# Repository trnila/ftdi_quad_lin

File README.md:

# FTDI Quad LIN

FTDI Quad-LIN is an FTDI-based board that enables communication with up to 4 LIN channels.

- 4x LIN master channels
- USB-C connector
- channel LED indication of power presence and communication activity
- power jack to power selected transceiver and its network

## Getting started
Install dkms driver for sllin module:
```
$ ./install_driver.sh
```

Then run following commands to:
- write given serial number into the device
- install a udev rule to start `ldattach@.service` on USB plug-in
- copy `sllin.network` file to automatically bringup `slcan` interface up

```
$ sudo apt install ftdi-eeprom
$ ./setup.sh some_serial_number
```

## Tests

Connect all channels to 2x PCAN-USB Pro, then install peak driver:
```sh
$ wget https://www.peak-system.com/quick/PLIN-Linux-Driver -O plin_linux_driver.tar.gz
$ tar -xf plin_linux_driver.tar.gz
$ cd peak-lin-driver-1.4.0
$ make
$ sudo make install
```

Then test all channels as masters by sending frames to the connected PCAN-USB device:
```
$ uv run pytest
```

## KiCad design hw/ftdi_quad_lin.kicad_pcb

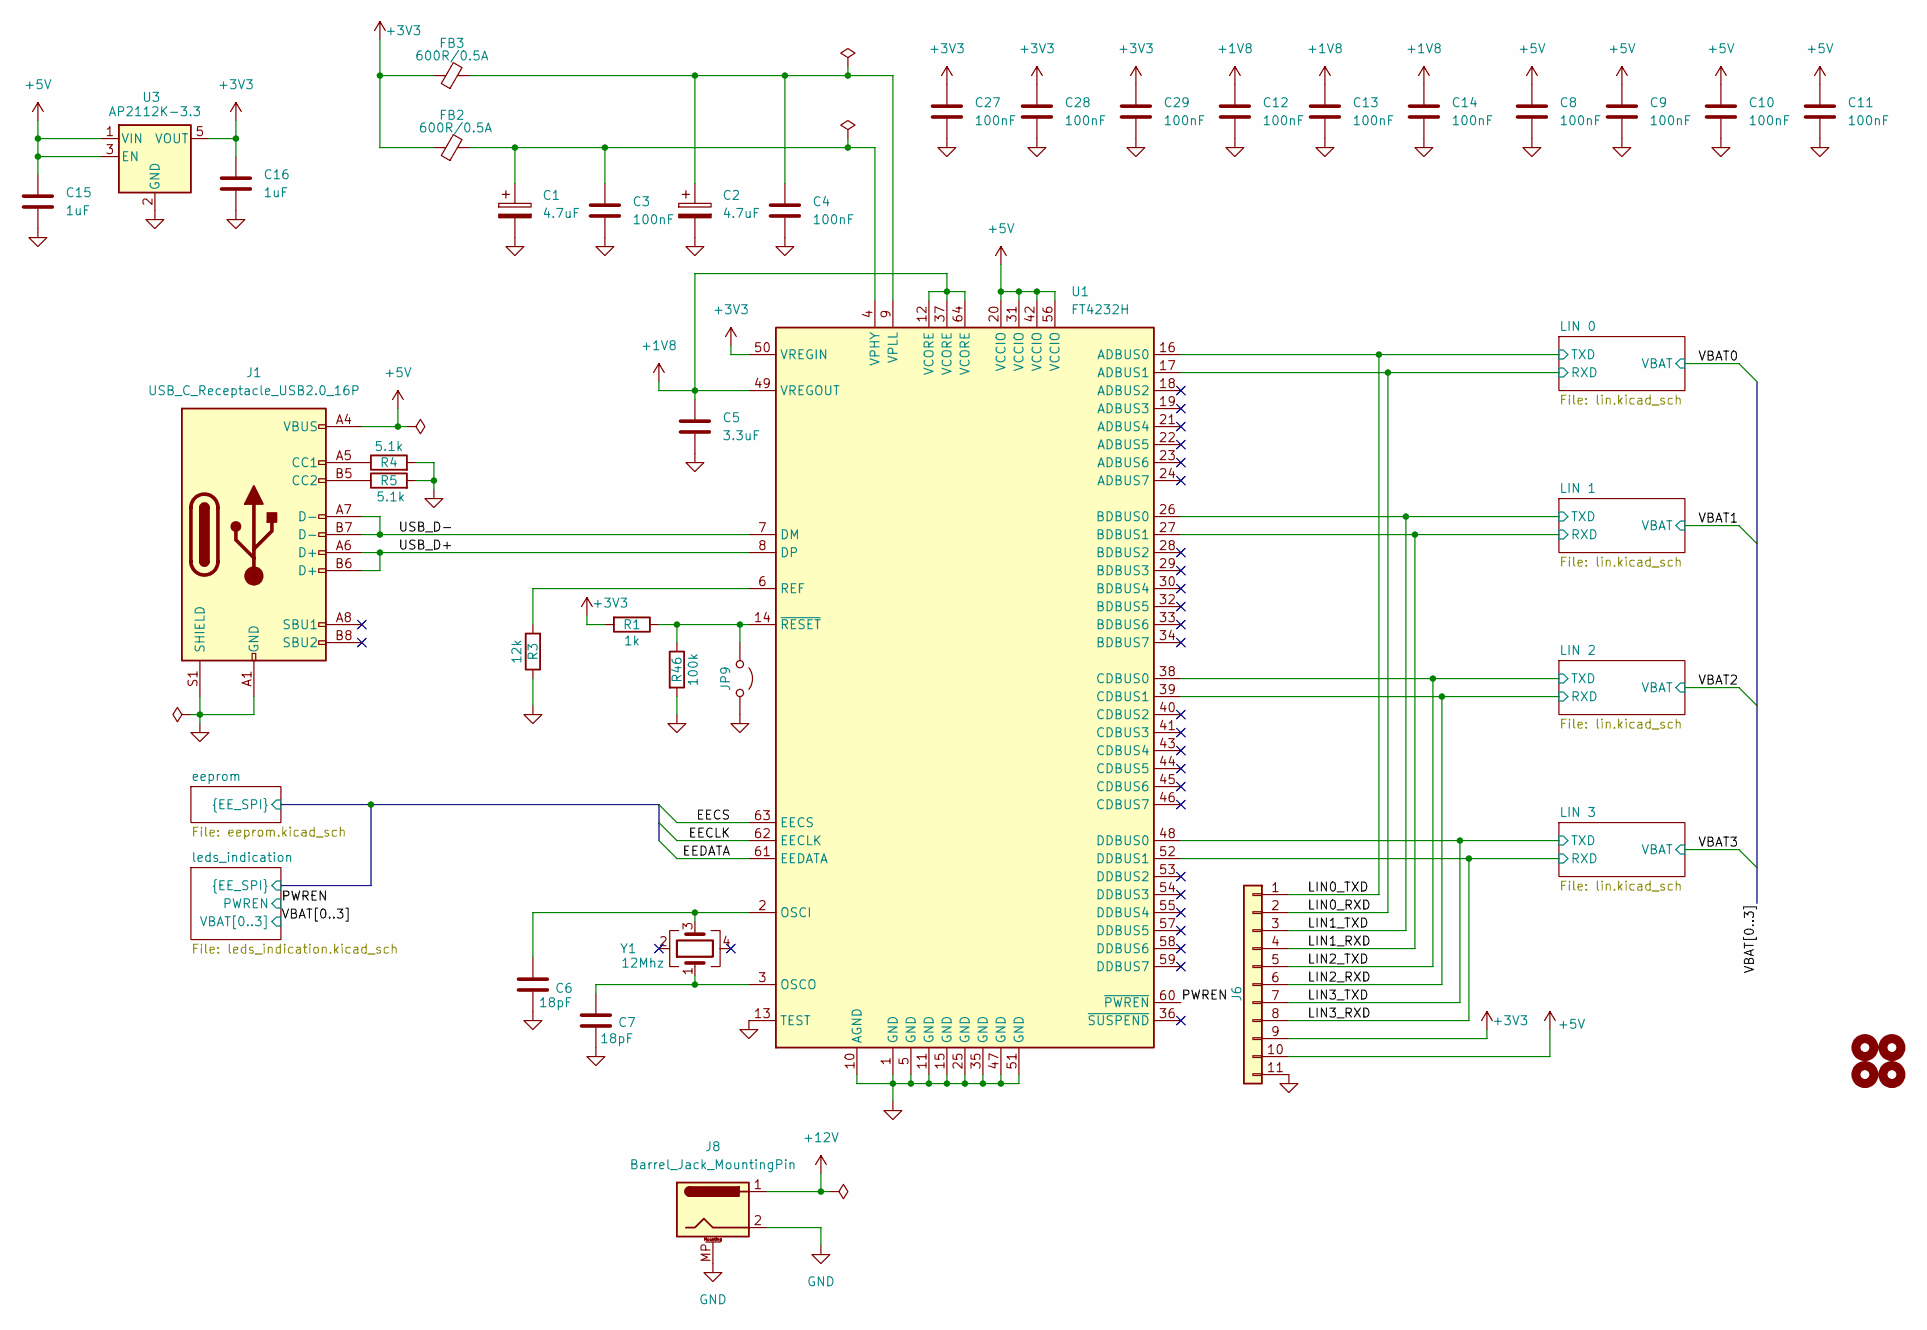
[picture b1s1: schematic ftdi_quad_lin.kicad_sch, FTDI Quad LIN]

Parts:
C1, C2: 4.7uF; C_1206_3216Metric_Pad1.33x1.80mm_HandSolder
C3, C4, C8, C9, C10, C11, C12, C13, C14, C27, C28, C29: 100nF; C_0805_2012Metric
C5: 3.3uF; C_0805_2012Metric
C6, C7: 18pF; C_0805_2012Metric
C15, C16: 1uF; C_0805_2012Metric
FB2, FB3: 600R/0.5A; L_0603_1608Metric_Pad1.05x0.95mm_HandSolder
H1, H2, H3, H4: MountingHole; MountingHole_3.2mm_M3
J1: USB_C_Receptacle_USB2.0_16P; USB_C_Receptacle_GCT_USB4105-xx-A_16P_TopMnt_Horizontal
J6: Conn_01x10; PinHeader_1x11_P2.54mm_Vertical
J8: Barrel_Jack_MountingPin; BarrelJack_CUI_PJ-063AH_Horizontal
JP9: Jumper_2_Open; TestPoint_2Pads_Pitch2.54mm_Drill0.8mm
R1: 1k; R_0805_2012Metric
R3: 12k; R_0805_2012Metric
R4, R5: 5.1k; R_0805_2012Metric
R46: 100k; R_0805_2012Metric
U1: FT4232H; LQFP-64_10x10mm_P0.5mm
U3: AP2112K-3.3; SOT-23-5_HandSoldering
Y1: 12Mhz; Crystal_SMD_TXC_7M-4Pin_3.2x2.5mm_HandSoldering

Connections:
+1V8: C5.1, C12.1, C13.1, C14.1, U1.12 (VCORE), U1.37 (VCORE), U1.49 (VREGOUT), U1.64 (VCORE)
+3V3: C16.1, C27.1, C28.1, C29.1, FB2.1, FB3.1, J6.9, R1.2, U1.50 (VREGIN), U3.5 (VOUT)
+5V: C8.1, C9.1, C10.1, C11.1, C15.1, J1.A4 (VBUS), J1.A9 (VBUS), J1.B4 (VBUS), J1.B9 (VBUS), J6.10, U1.20 (VCCIO), U1.31 (VCCIO), U1.42 (VCCIO), U1.56 (VCCIO), U3.1 (VIN), U3.3 (EN); also elsewhere on the board
+12V: J8.1; also elsewhere on the board
/LIN0_RXD: J6.2, U1.17 (ADBUS1); also elsewhere on the board
/LIN0_TXD: J6.1, U1.16 (ADBUS0); also elsewhere on the board
/LIN1_RXD: J6.4, U1.27 (BDBUS1); also elsewhere on the board
/LIN1_TXD: J6.3, U1.26 (BDBUS0); also elsewhere on the board
/LIN2_RXD: J6.6, U1.39 (CDBUS1); also elsewhere on the board
/LIN2_TXD: J6.5, U1.38 (CDBUS0); also elsewhere on the board
/LIN3_RXD: J6.8, U1.52 (DDBUS1); also elsewhere on the board
/LIN3_TXD: J6.7, U1.48 (DDBUS0); also elsewhere on the board
/PWREN: U1.60 (~PWREN); also elsewhere on the board
/USB_D+: J1.A6 (D+), J1.B6 (D+), U1.8 (DP)
/USB_D-: J1.A7 (D-), J1.B7 (D-), U1.7 (DM)
/eeprom/EECLK: U1.62 (EECLK); also elsewhere on the board
/eeprom/EECS: U1.63 (EECS); also elsewhere on the board
/eeprom/EEDATA: U1.61 (EEDATA); also elsewhere on the board
GND: C1.2, C2.2, C3.2, C4.2, C5.2, C6.2, C7.2, C8.2, C9.2, C10.2, C11.2, C12.2, C13.2, C14.2, C15.2, C16.2, C27.2, C28.2, C29.2, J1.A1 (GND), J1.A12 (GND), J1.B1 (GND), J1.B12 (GND), J1.S1 (SHIELD), J6.11, J8.2, J8.MP (MountPin), JP9.2 (B), R3.1, R4.2, R5.2, R46.2, U1.1 (GND), U1.5 (GND), U1.10 (AGND), U1.11 (GND), U1.13 (TEST), U1.15 (GND), U1.25 (GND), U1.35 (GND), U1.47 (GND), U1.51 (GND), U3.2 (GND); also elsewhere on the board
unnamed: J1.A5 (CC1), R4.1
unnamed: J1.B5 (CC2), R5.1
unnamed: JP9.1 (A), R1.1, R46.1, U1.14 (~RESET)
unnamed: C6.1, U1.2 (OSCI), Y1.3
unnamed: C7.1, U1.3 (OSCO), Y1.1
unnamed: R3.2, U1.6 (REF)
unnamed: C1.1, C3.1, FB2.2, U1.4 (VPHY)
unnamed: C2.1, C4.1, FB3.2, U1.9 (VPLL)

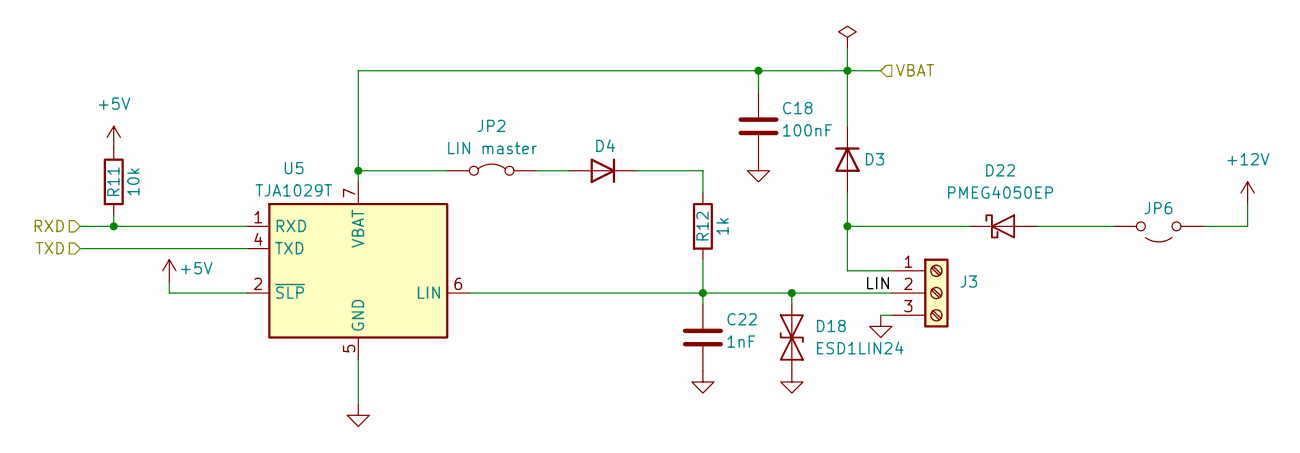
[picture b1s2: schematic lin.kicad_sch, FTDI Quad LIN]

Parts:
C18: 100nF; C_0805_2012Metric
C22: 1nF; C_0805_2012Metric
D3, D4: D_SOD-323_HandSoldering
D18: ESD1LIN24; D_SOD-323_HandSoldering
D22: PMEG4050EP; Nexperia_CFP3_SOD-123W
J3: Screw_Terminal_01x03; lin_connector
JP2: LIN master; TestPoint_2Pads_Pitch2.54mm_Drill0.8mm
JP6: Jumper_2_Open; TestPoint_2Pads_Pitch2.54mm_Drill0.8mm
R11: 10k; R_0805_2012Metric
R12: 1k; R_0805_2012Metric
U5: TJA1029T; SOIC-8_3.9x4.9mm_P1.27mm

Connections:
+5V: R11.1, U5.2 (~SLP); also elsewhere on the board
+12V: JP6.1 (A); also elsewhere on the board
/LIN1_RXD: R11.2, U5.1 (RXD); also elsewhere on the board
/LIN1_TXD: U5.4 (TXD); also elsewhere on the board
/LIN 1/LIN: C22.1, D18.2 (A2), J3.2, R12.2, U5.6 (LIN)
/VBAT1: C18.1, D3.1 (K), JP2.1 (A), U5.7 (VBAT); also elsewhere on the board
GND: C18.2, C22.2, D18.1 (A1), J3.3, U5.5 (GND); also elsewhere on the board
unnamed: D4.2 (A), JP2.2 (B)
unnamed: D4.1 (K), R12.1
unnamed: D22.2 (A), JP6.2 (B)
unnamed: D3.2 (A), D22.1 (K), J3.1

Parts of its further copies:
C17, C19, C20: 100nF; C_0805_2012Metric
C21, C23, C24: 1nF; C_0805_2012Metric
D1, D2, D5, D6, D7, D8: D_SOD-323_HandSoldering
D9, D19, D20: ESD1LIN24; D_SOD-323_HandSoldering
D21, D23, D24: PMEG4050EP; Nexperia_CFP3_SOD-123W
J2, J4, J5: Screw_Terminal_01x03; lin_connector
JP1, JP3, JP4: LIN master; TestPoint_2Pads_Pitch2.54mm_Drill0.8mm
JP5, JP7, JP8: Jumper_2_Open; TestPoint_2Pads_Pitch2.54mm_Drill0.8mm
R9, R13, R15: 10k; R_0805_2012Metric
R10, R14, R16: 1k; R_0805_2012Metric
U2, U6, U7: TJA1029T; SOIC-8_3.9x4.9mm_P1.27mm

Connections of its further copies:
+5V: R9.1, R13.1, R15.1, U2.2 (~SLP), U6.2 (~SLP), U7.2 (~SLP); also elsewhere on the board
+12V: JP5.1 (A), JP7.1 (A), JP8.1 (A); also elsewhere on the board
/LIN0_RXD: R9.2, U2.1 (RXD); also elsewhere on the board
/LIN0_TXD: U2.4 (TXD); also elsewhere on the board
/LIN2_RXD: R13.2, U6.1 (RXD); also elsewhere on the board
/LIN2_TXD: U6.4 (TXD); also elsewhere on the board
/LIN3_RXD: R15.2, U7.1 (RXD); also elsewhere on the board
/LIN3_TXD: U7.4 (TXD); also elsewhere on the board
/LIN 0/LIN: C21.1, D9.2 (A2), J2.2, R10.2, U2.6 (LIN)
/LIN 2/LIN: C23.1, D19.2 (A2), J4.2, R14.2, U6.6 (LIN)
/LIN 3/LIN: C24.1, D20.2 (A2), J5.2, R16.2, U7.6 (LIN)
/VBAT0: C17.1, D1.1 (K), JP1.1 (A), U2.7 (VBAT); also elsewhere on the board
/VBAT2: C19.1, D5.1 (K), JP3.1 (A), U6.7 (VBAT); also elsewhere on the board
/VBAT3: C20.1, D7.1 (K), JP4.1 (A), U7.7 (VBAT); also elsewhere on the board
GND: C17.2, C19.2, C20.2, C21.2, C23.2, C24.2, D9.1 (A1), D19.1 (A1), D20.1 (A1), J2.3, J4.3, J5.3, U2.5 (GND), U6.5 (GND), U7.5 (GND); also elsewhere on the board
unnamed: D1.2 (A), D21.1 (K), J2.1
unnamed: D2.2 (A), JP1.2 (B)
unnamed: D2.1 (K), R10.1
unnamed: D6.2 (A), JP3.2 (B)
unnamed: D6.1 (K), R14.1
unnamed: D8.2 (A), JP4.2 (B)
unnamed: D8.1 (K), R16.1
unnamed: D21.2 (A), JP5.2 (B)
unnamed: D23.2 (A), JP7.2 (B)
unnamed: D5.2 (A), D23.1 (K), J4.1
unnamed: D24.2 (A), JP8.2 (B)
unnamed: D7.2 (A), D24.1 (K), J5.1

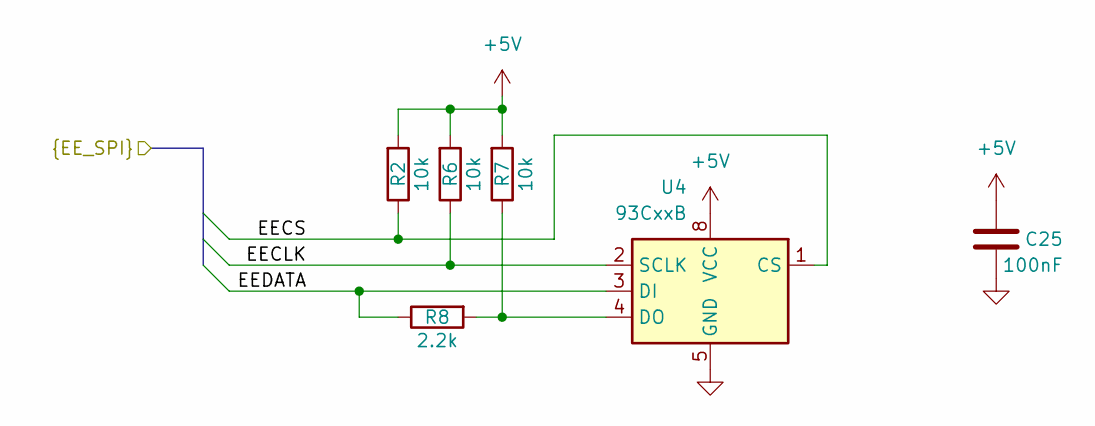
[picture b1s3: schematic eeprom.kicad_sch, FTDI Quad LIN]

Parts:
C25: 100nF; C_0805_2012Metric
R2, R6, R7: 10k; R_0805_2012Metric
R8: 2.2k; R_0805_2012Metric
U4: 93CxxB; SOIC-8_3.9x4.9mm_P1.27mm

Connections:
+5V: C25.1, R2.2, R6.2, R7.2, U4.8 (VCC); also elsewhere on the board
/eeprom/EECLK: R6.1, U4.2 (SCLK); also elsewhere on the board
/eeprom/EECS: R2.1, U4.1 (CS); also elsewhere on the board
/eeprom/EEDATA: R8.1, U4.3 (DI); also elsewhere on the board
GND: C25.2, U4.5 (GND); also elsewhere on the board
unnamed: R7.1, R8.2, U4.4 (DO)

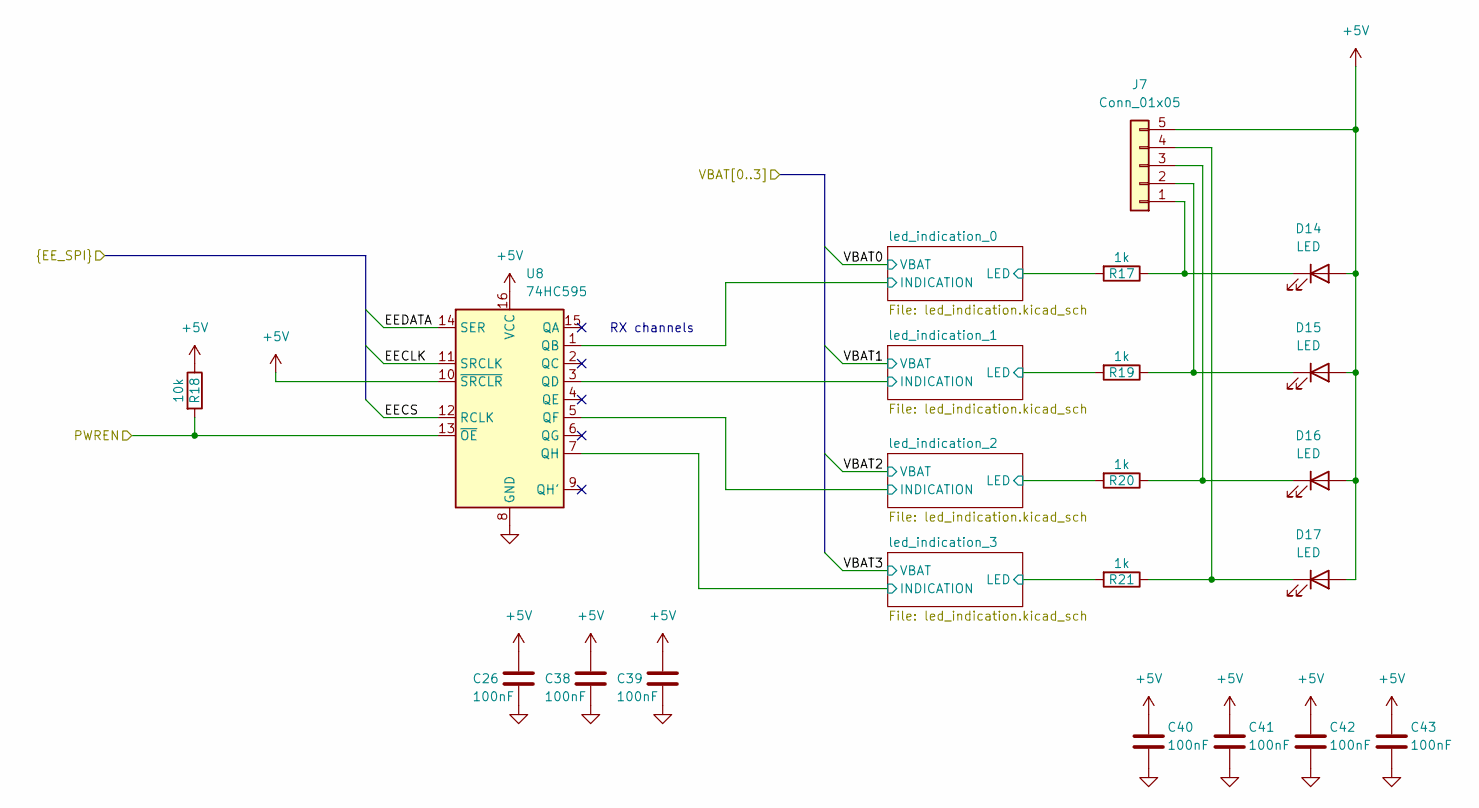
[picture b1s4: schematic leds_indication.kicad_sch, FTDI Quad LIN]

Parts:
C26, C38, C39, C40, C41, C42, C43: 100nF; C_0805_2012Metric
D14, D15, D16, D17: LED; 1216.1002
J7: Conn_01x05; JST_XH_B5B-XH-A_1x05_P2.50mm_Vertical
R17, R19, R20, R21: 1k; R_0805_2012Metric
R18: 10k; R_0805_2012Metric
U8: 74HC595; SOIC-16_3.9x9.9mm_P1.27mm

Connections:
+5V: C26.1, C38.1, C39.1, C40.1, C41.1, C42.1, C43.1, D14.2 (A), D15.2 (A), D16.2 (A), D17.2 (A), J7.5, R18.1, U8.10 (~SRCLR), U8.16 (VCC); also elsewhere on the board
/PWREN: R18.2, U8.13 (~OE); also elsewhere on the board
/eeprom/EECLK: U8.11 (SRCLK); also elsewhere on the board
/eeprom/EECS: U8.12 (RCLK); also elsewhere on the board
/eeprom/EEDATA: U8.14 (SER); also elsewhere on the board
/leds_indication/led_indication_0/INDICATION: U8.1 (QB); also elsewhere on the board
/leds_indication/led_indication_0/LED: R17.2; also elsewhere on the board
/leds_indication/led_indication_1/INDICATION: U8.3 (QD); also elsewhere on the board
/leds_indication/led_indication_1/LED: R19.2; also elsewhere on the board
/leds_indication/led_indication_2/INDICATION: U8.5 (QF); also elsewhere on the board
/leds_indication/led_indication_2/LED: R20.2; also elsewhere on the board
/leds_indication/led_indication_3/INDICATION: U8.7 (QH); also elsewhere on the board
/leds_indication/led_indication_3/LED: R21.2; also elsewhere on the board
GND: C26.2, C38.2, C39.2, C40.2, C41.2, C42.2, C43.2, U8.8 (GND); also elsewhere on the board
unnamed: D14.1 (K), J7.1, R17.1
unnamed: D15.1 (K), J7.2, R19.1
unnamed: D16.1 (K), J7.3, R20.1
unnamed: D17.1 (K), J7.4, R21.1

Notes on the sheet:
RX channels

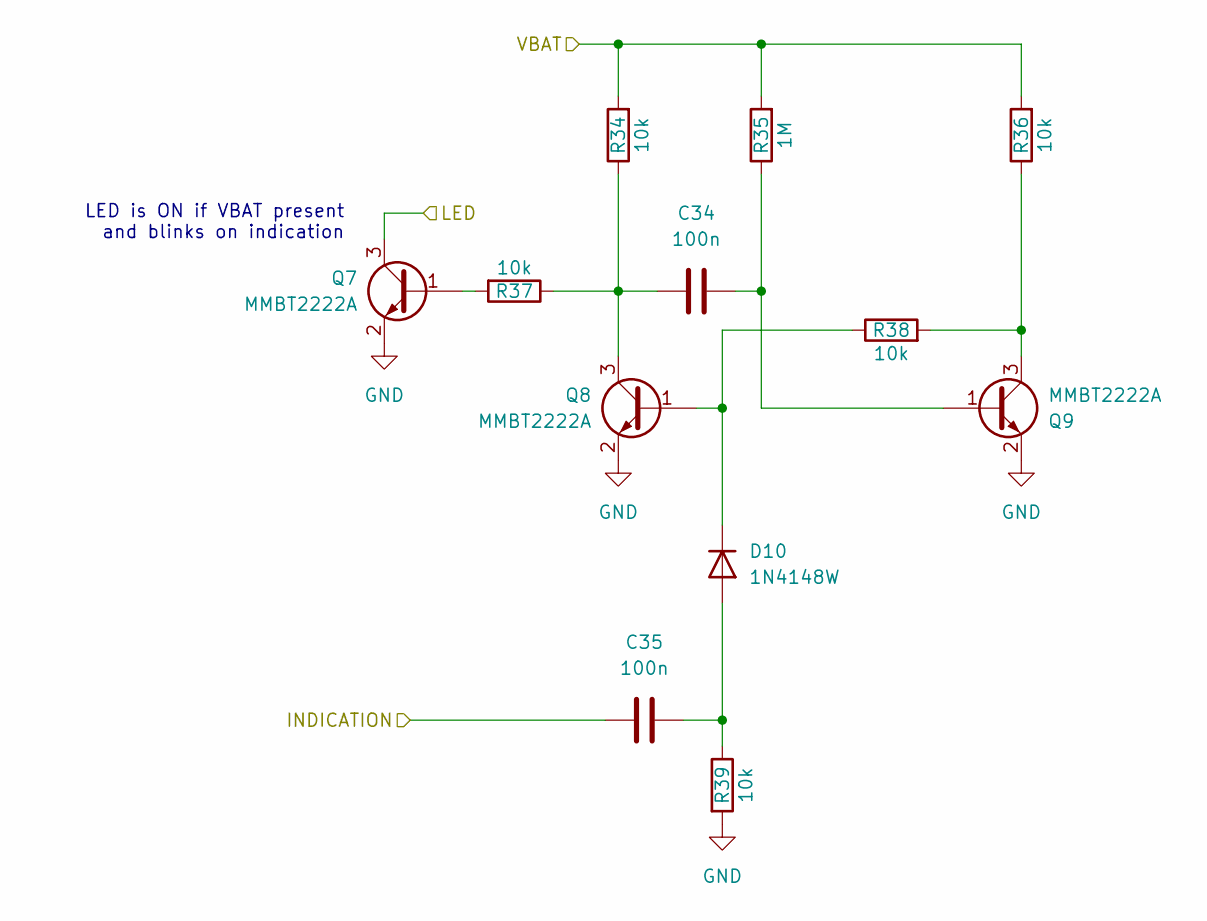
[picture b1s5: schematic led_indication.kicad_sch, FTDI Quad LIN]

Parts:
C34, C35: 100n; C_0805_2012Metric_Pad1.18x1.45mm_HandSolder
D10: 1N4148W; D_SOD-323_HandSoldering
Q7, Q8, Q9: MMBT2222A; SOT-23
R34, R36, R37, R38, R39: 10k; R_0805_2012Metric
R35: 1M; R_0805_2012Metric

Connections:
/VBAT2: R34.2, R35.2, R36.2; also elsewhere on the board
/leds_indication/led_indication_2/INDICATION: C35.1; also elsewhere on the board
/leds_indication/led_indication_2/LED: Q7.3 (C); also elsewhere on the board
GND: Q7.2 (E), Q8.2 (E), Q9.2 (E), R39.2; also elsewhere on the board
unnamed: C35.2, D10.2 (A), R39.1
unnamed: D10.1 (K), Q8.1 (B), R38.1
unnamed: Q7.1 (B), R37.2
unnamed: C34.1, Q8.3 (C), R34.1, R37.1
unnamed: C34.2, Q9.1 (B), R35.1
unnamed: Q9.3 (C), R36.1, R38.2

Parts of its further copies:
C30, C31, C32, C33, C36, C37: 100n; C_0805_2012Metric_Pad1.18x1.45mm_HandSolder
D11, D12, D13: 1N4148W; D_SOD-323_HandSoldering
Q1, Q2, Q3, Q4, Q5, Q6, Q10, Q11, Q12: MMBT2222A; SOT-23
R22, R24, R25, R26, R27, R28, R30, R31, R32, R33, R40, R42, R43, R44, R45: 10k; R_0805_2012Metric
R23, R29, R41: 1M; R_0805_2012Metric

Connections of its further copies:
/VBAT0: R22.2, R23.2, R24.2; also elsewhere on the board
/VBAT1: R28.2, R29.2, R30.2; also elsewhere on the board
/VBAT3: R40.2, R41.2, R42.2; also elsewhere on the board
/leds_indication/led_indication_0/INDICATION: C31.1; also elsewhere on the board
/leds_indication/led_indication_0/LED: Q1.3 (C); also elsewhere on the board
/leds_indication/led_indication_1/INDICATION: C33.1; also elsewhere on the board
/leds_indication/led_indication_1/LED: Q4.3 (C); also elsewhere on the board
/leds_indication/led_indication_3/INDICATION: C37.1; also elsewhere on the board
/leds_indication/led_indication_3/LED: Q10.3 (C); also elsewhere on the board
GND: Q1.2 (E), Q2.2 (E), Q3.2 (E), Q4.2 (E), Q5.2 (E), Q6.2 (E), Q10.2 (E), Q11.2 (E), Q12.2 (E), R27.2, R33.2, R45.2; also elsewhere on the board
unnamed: C31.2, D11.2 (A), R27.1
unnamed: D11.1 (K), Q2.1 (B), R26.1
unnamed: C33.2, D12.2 (A), R33.1
unnamed: D12.1 (K), Q5.1 (B), R32.1
unnamed: C37.2, D13.2 (A), R45.1
unnamed: D13.1 (K), Q11.1 (B), R44.1
unnamed: Q1.1 (B), R25.2
unnamed: C30.1, Q2.3 (C), R22.1, R25.1
unnamed: C30.2, Q3.1 (B), R23.1
unnamed: Q3.3 (C), R24.1, R26.2
unnamed: Q4.1 (B), R31.2
unnamed: C32.1, Q5.3 (C), R28.1, R31.1
unnamed: C32.2, Q6.1 (B), R29.1
unnamed: Q6.3 (C), R30.1, R32.2
unnamed: Q10.1 (B), R43.2
unnamed: C36.1, Q11.3 (C), R40.1, R43.1
unnamed: C36.2, Q12.1 (B), R41.1
unnamed: Q12.3 (C), R42.1, R44.2

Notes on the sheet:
LED is ON if VBAT present and blinks on indication

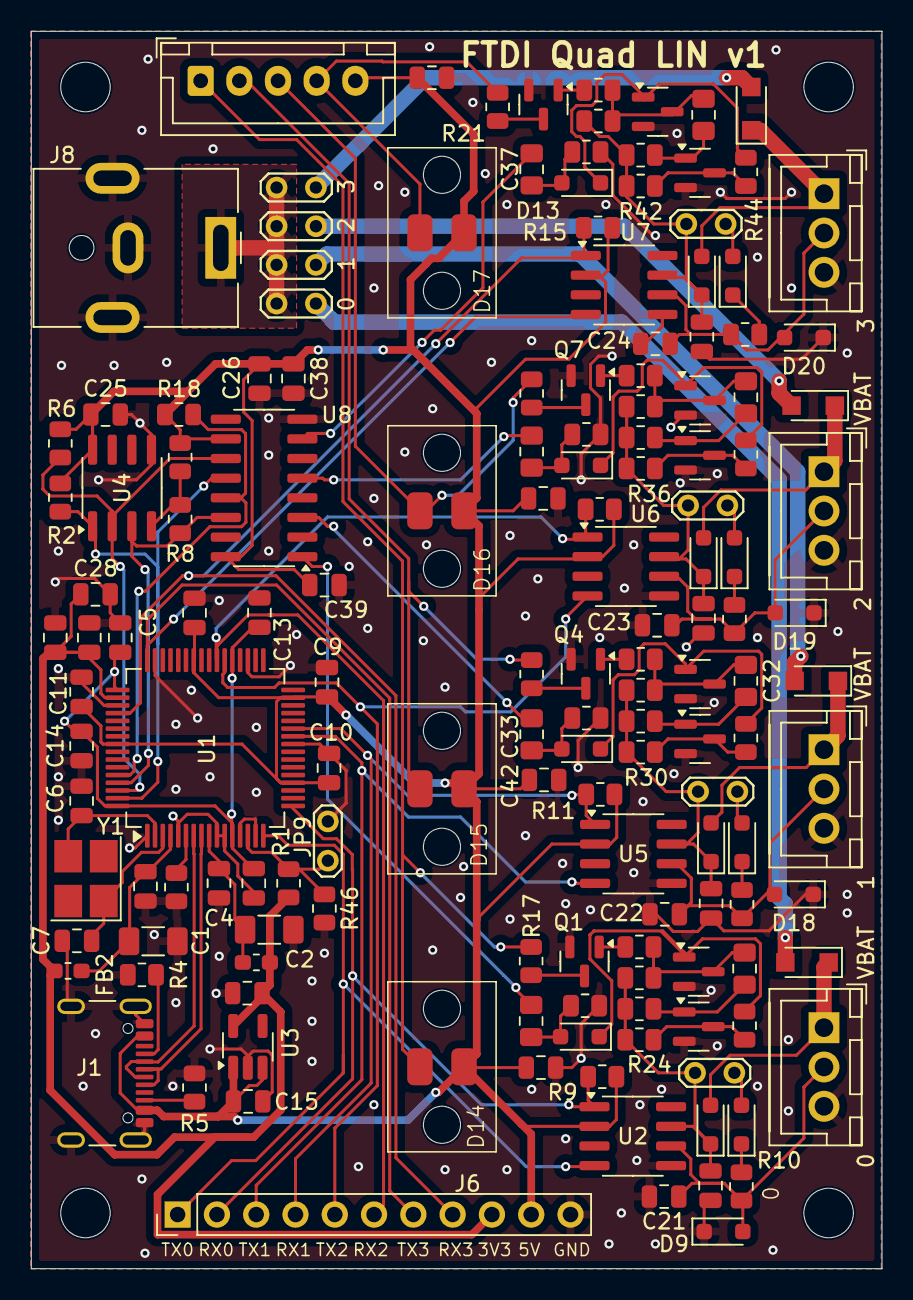
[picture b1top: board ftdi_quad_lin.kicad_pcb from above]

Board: 2 copper layers, 55.0 x 80.0 mm, 157 parts (0 on the bottom side), 88 nets.

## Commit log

2025-01-04 routed
2025-01-05 finito
2025-01-05 renamed
2025-01-05 reoredered
2025-01-20 Using bus
2025-01-25 progress
2025-01-25 new connectors
2025-01-25 reworking
2025-01-25 yep crash
2025-01-25 before givinr resistors
2025-01-25 routing details
2025-01-25 all connected
2025-01-25 labels
2025-01-25 okay?
2025-01-25 removed library
2025-01-25 Added manfs
2025-01-25 regen
2025-01-26 rozmery
2025-01-26 pulldown reset
2025-01-26 fixin mes g
2025-01-26 power checked
2025-01-26 updated libs
2025-01-26 more capacitors
2025-01-26 added ESD protection to lin
2025-01-26 docs
2025-01-26 1M ohm
2025-01-26 fix orientation of scre
2025-01-26 Added power diodes
2025-01-26 Moved to hw directory
2025-01-26 nothing
2025-01-26 config gor jclpcb
2025-01-26 fixes
2025-03-14 hw: initial commit
2025-03-14 hw: manf for jack
2025-03-14 hw: manf for LIN connector
2025-03-14 hw: manf for USB
2025-03-14 hw: manf for PMEG4050EP,115
2025-03-14 hw: BOM settings
2025-03-14 hw: added pdf schematics
2025-03-14 hw: led RC changed 220n->100n
2025-03-14 Added README.md
2025-03-30 initial case
2025-03-30 added flake.nix
2025-03-30 socket
2025-03-30 final
2025-03-30 added shell.nix
2025-03-30 removed flake.ni
2025-03-30 first version
2025-03-31 torelance
2025-03-31 tolerances
2025-03-31 Revert "tolerances"
    This reverts commit 8fc8ae173fe1e3db279f2eaec13820490f4d6e29.
2025-03-31 Revert "torelance"
    This reverts commit b74345672f38183a8c2c520d297c0efa9a197849.
2025-04-01 barrel jack hole
2025-04-01 tolerances of base
2025-04-01 fix holes to usb/dc jack
2025-04-01 rotate assembly
2025-04-01 screw Dsub
2025-04-01 heated end + screws
2025-04-01 final final?
2025-04-03 button dimensions
2025-04-03 final final
2025-06-15 Add pre-commit
2025-06-15 install.sh to install dkms sllin
2025-06-15 autobring up
2025-06-15 hw tests
2025-07-16 README.md: describe how to install testing peak driver
2025-07-16 README.md: added case photo
